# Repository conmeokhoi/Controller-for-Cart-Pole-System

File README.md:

# 150W Isolated Cart-Pole Control Board (STM32)

## 📌 Project Overview
This project presents the design and implementation of a specialized control board for an Inverted Pendulum on a Cart (Cart-Pole) system. It serves as a benchmark for testing cascaded control strategies in highly non-linear, unstable, and under-actuated environments.

## 🛠 Hardware Architecture

### 1. Multi-Stage Power Management
The system operates on a primary **24V DC** input with hierarchical regulation to ensure signal stability and efficiency:
* **12V Rail**: Regulated by the **L7812** for MOSFET gate drivers.
* **5V Auxiliary Rail**: Stepped down via a high-efficiency **TPS5430 Buck Converter** (~90% efficiency) to power encoders and sensors.
* **Isolated 3.3V Logic**: Utilizes a **B0505S** isolated DC-DC converter and an **AMS1117-3.3** LDO to shield the MCU from power-stage inductive switching noise.

### 2. Motor Drive Stage (150W H-Bridge)
* **MOSFET Selection**: Features four **IRF3205S** N-channel MOSFETs with an exceptionally low $R_{DS(on)} \approx 8 m\Omega$ to minimize conduction losses.
* **Gate Driving**: Employs **IR2104** drivers with bootstrap circuitry to maintain high-side gate saturation.
* **Safety Logic**: Integrated **520ns hardware dead-time** prevents "shoot-through" short circuits.

### 3. Galvanic Isolation
* **High-Speed Paths**: **6N137 optocouplers** (10Mbps) are dedicated to PWM and Encoder signals to prevent propagation delay in the real-time control loop.
* **Isolation Barrier**: Complete physical partitioning between the Power Zone and Clean Logic Zone via the optocoupler bridge.

## 💻 Firmware & Control Logic
Powered by the **STM32F103C8T6** (ARM Cortex-M3) at **72MHz**:
* **Encoder Processing**: Utilizes hardware Timer Encoder Mode for high-resolution quadrature decoding without CPU overhead.
* **PWM Configuration**: Frequency set at **20kHz** to eliminate audible jitter and provide granular torque control:
  $$f_{PWM} = \frac{f_{CLK}}{(PSC+1) \times (ARR+1)} = \frac{72,000,000}{36 \times 100} = 20,000 \text{ Hz}$$
* **Control Algorithm**: Implements a **Cascaded PID** structure where the outer loop manages cart position and the inner loop stabilizes the pendulum angle.

## 🔍 Failure Analysis (Root Cause)
During integration, a hardware breakdown occurred in the H-bridge. Forensic analysis identified a missing connection between the **VS pin** (Pin 6) of the IR2104 drivers and the **source terminals** of the high-side MOSFETs.This led to a "floating gate" state, causing a direct short-circuit from the 24V rail to Ground.

## 🎥 Experimental Validation
The following video demonstrates the individual functional verification of the control board:
* **Hardware Self-Test:** Verification of the 24V, 12V, 5V, and 3.3V power rails.
* **Encoder & Sensor Feedback:** Real-time pulse capturing and gyroscope data retrieval.
* **PWM Output:** Validation of 20kHz complementary signals via oscilloscope.
* **Video Demo:** 

---
**Author**: Nguyễn Huỳnh Khôi.  
**Supervised by**: PhD. Võ Lâm Chương.   
**University**: Ho Chi Minh City University of Technology and Engineering (HCMUTE)

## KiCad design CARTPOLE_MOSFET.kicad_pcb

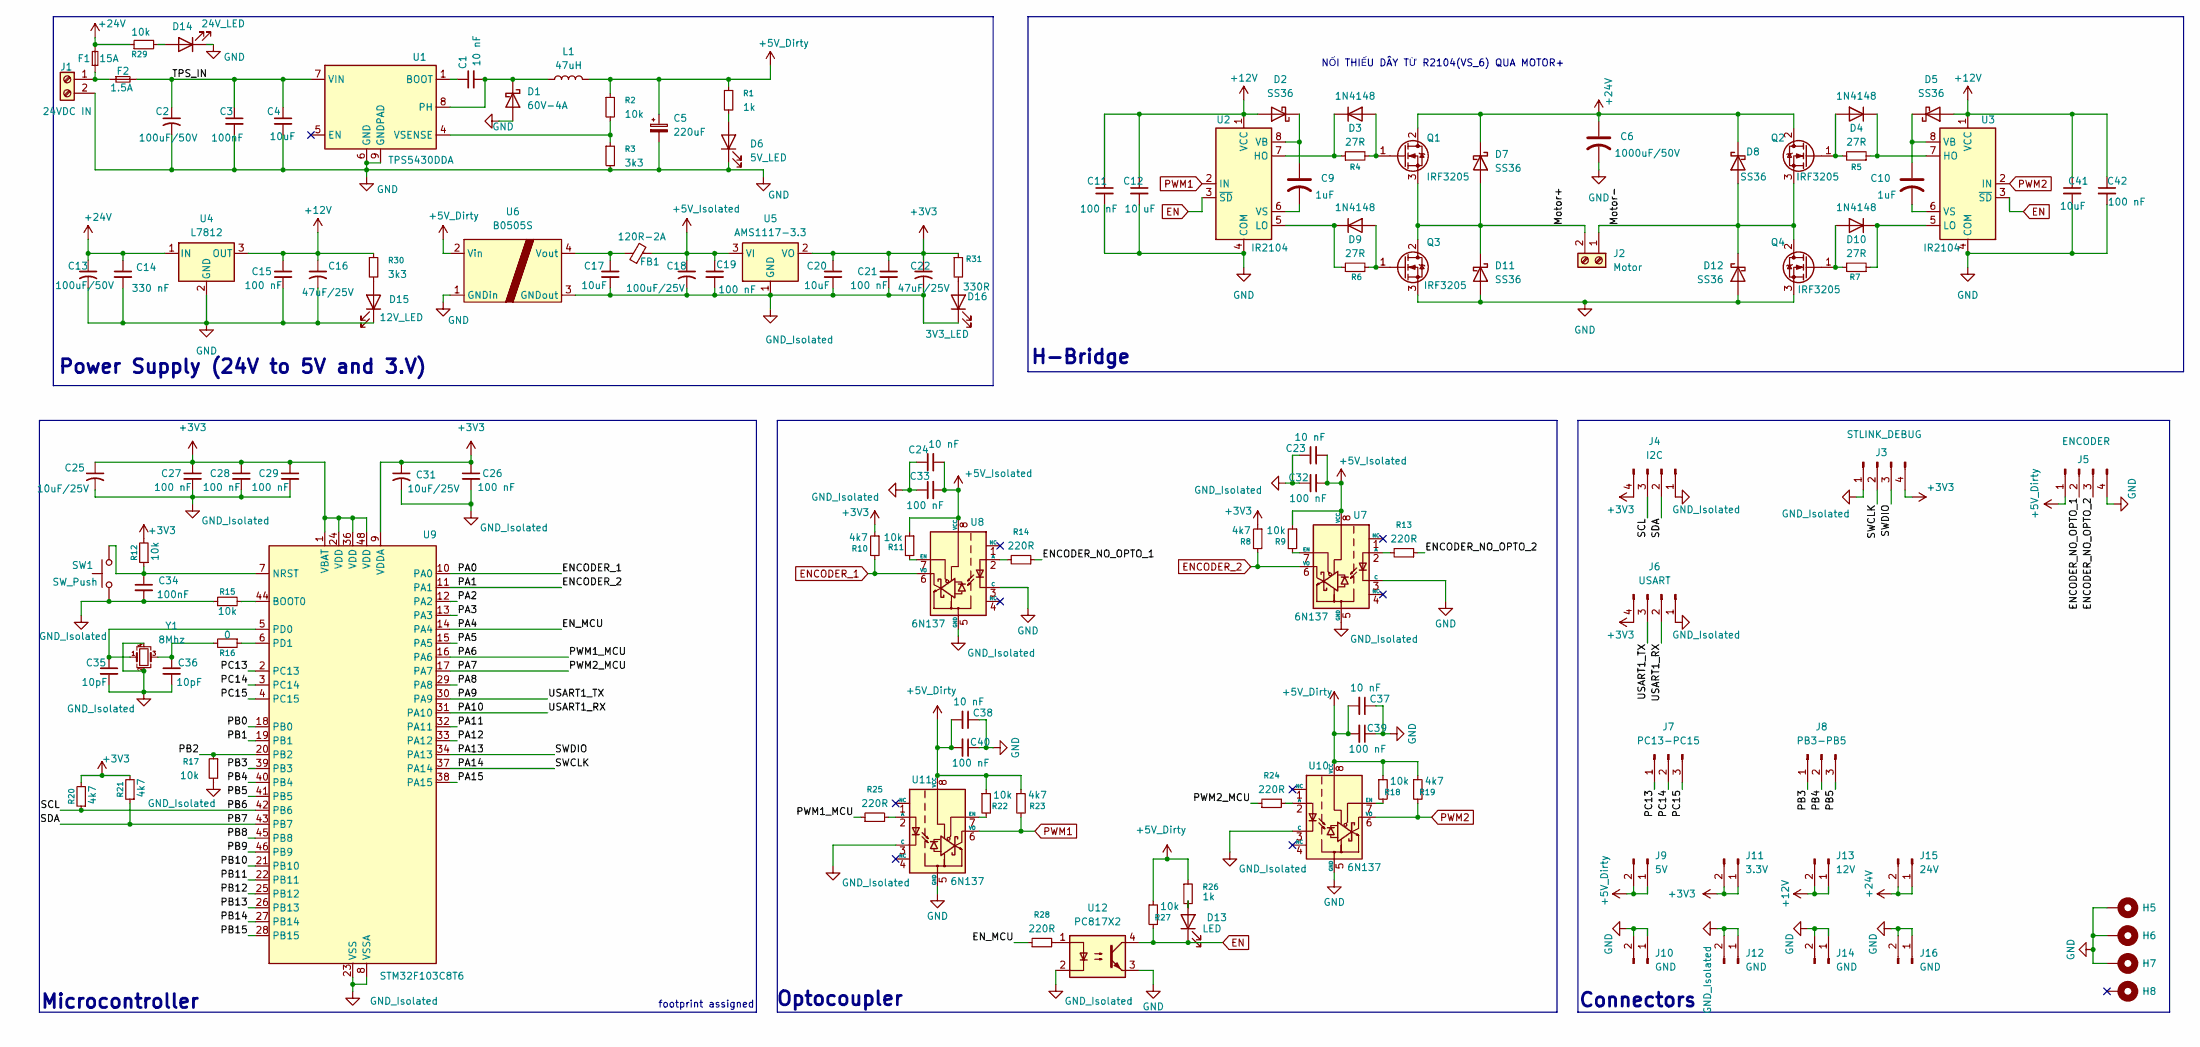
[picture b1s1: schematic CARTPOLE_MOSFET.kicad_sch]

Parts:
C1, C23, C24, C37, C38: 10 nF; C_0805_2012Metric_Pad1.18x1.45mm_HandSolder
C2, C13: 100uF/50V; CP_Elec_8x10.5
C3: 100nF; C_0805_2012Metric_Pad1.18x1.45mm_HandSolder
C4, C17, C20, C41: 10uF; C_0805_2012Metric_Pad1.18x1.45mm_HandSolder
C5: 220uF; CP_Elec_8x10.5
C6: 1000uF/50V; C_Radial_D12.5mm_H25.0mm_P5.00mm
C9, C10: 1uF; C_0805_2012Metric_Pad1.18x1.45mm_HandSolder
C11, C15, C19, C21, C32, C33, C39, C40, C42: 100 nF; C_0805_2012Metric_Pad1.18x1.45mm_HandSolder
C12: 10 uF; C_0805_2012Metric_Pad1.18x1.45mm_HandSolder
C14: 330 nF; C_0805_2012Metric_Pad1.18x1.45mm_HandSolder
C16, C22: 47uF/25V; CP_Elec_6.3x5.4
C18: 100uF/25V; CP_Elec_8x10.5
C25, C31: 10uF/25V; C_0603_1608Metric
C26, C27, C28, C29: 100 nF; C_0603_1608Metric
C34: 100nF; C_0603_1608Metric
C35, C36: 10pF; C_0603_1608Metric
D1: 60V-4A; D_SMB
D2, D5, D7, D8, D11, D12: SS36; D_SMA_Handsoldering
D3, D4, D9, D10: 1N4148; D_SOD-123
D6: 5V_LED; LED_0805_2012Metric_Pad1.15x1.40mm_HandSolder
D13: LED; LED_0805_2012Metric_Pad1.15x1.40mm_HandSolder
D14: 24V_LED; LED_0805_2012Metric_Pad1.15x1.40mm_HandSolder
D15: 12V_LED; LED_0805_2012Metric_Pad1.15x1.40mm_HandSolder
D16: 3V3_LED; LED_0805_2012Metric_Pad1.15x1.40mm_HandSolder
F1: 15A; Fuseholder_Littelfuse_Nano2_154x
F2: 1.5A; Fuseholder_Littelfuse_Nano2_154x
FB1: 120R-2A; C_0805_2012Metric_Pad1.18x1.45mm_HandSolder
H5, H6, H7, H8: MountingHole_3.2mm_M3_Pad_Via
J1: 24VDC IN; TerminalBlock_Ningbo-Kagnex_HB9500_1x02_P9.5mm
J2: Motor; TerminalBlock_Ningbo-Kagnex_HB9500_1x02_P9.5mm
J3: STLINK_DEBUG; PinHeader_1x04_P2.54mm_Vertical
J4: I2C; PinHeader_1x04_P2.54mm_Vertical
J5: ENCODER; PinHeader_1x04_P2.54mm_Vertical
J6: USART; PinHeader_1x04_P2.54mm_Vertical
J7: PC13-PC15; PinHeader_1x03_P2.54mm_Vertical
J8: PB3-PB5; PinHeader_1x03_P2.54mm_Vertical
J9: 5V; PinHeader_1x02_P2.54mm_Vertical
J10, J12, J14, J16: GND; PinHeader_1x02_P2.54mm_Vertical
J11: 3.3V; PinHeader_1x02_P2.54mm_Vertical
J13: 12V; PinHeader_1x02_P2.54mm_Vertical
J15: 24V; PinHeader_1x02_P2.54mm_Vertical
L1: 47uH; INDPM120120X800N
Q1, Q2, Q3, Q4: IRF3205; TO-263-2
R1, R26: 1k; R_0805_2012Metric_Pad1.20x1.40mm_HandSolder
R2, R9, R11, R18, R22, R27, R29: 10k; R_0805_2012Metric_Pad1.20x1.40mm_HandSolder
R3, R30: 3k3; R_0805_2012Metric_Pad1.20x1.40mm_HandSolder
R4, R5, R6, R7: 27R; R_0805_2012Metric_Pad1.20x1.40mm_HandSolder
R8, R10, R19, R23: 4k7; R_0805_2012Metric_Pad1.20x1.40mm_HandSolder
R12, R15, R17: 10k; C_0603_1608Metric
R13, R14, R24, R25, R28: 220R; R_0805_2012Metric_Pad1.20x1.40mm_HandSolder
R16: 0; C_0603_1608Metric
R20, R21: 4k7; R_0603_1608Metric
R31: 330R; R_0805_2012Metric_Pad1.20x1.40mm_HandSolder
SW1: SW_Push; SW_SPST_CK_RS282G05A3
U1: TPS5430DDA; TI_SO-PowerPAD-8_ThermalVias
U2, U3: IR2104; SOIC-8_3.9x4.9mm_P1.27mm
U4: L7812; TO-220-3_Vertical
U5: AMS1117-3.3; SOT-223-3_TabPin2
U6: B0505S; CONV_RFM-0505S
U7, U8, U10, U11: 6N137; SMDIP-8_W9.53mm_Clearance8mm
U9: STM32F103C8T6; LQFP-48_7x7mm_P0.5mm
U12: PC817X2; SOP254P975X460-4N
Y1: 8Mhz; Crystal_SMD_3225-4Pin_3.2x2.5mm

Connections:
+3V3: C20.1, C21.1, C22.1, C25.1, C26.1, C27.1, C28.1, C29.1, C31.1, J3.4, J4.4, J6.4, J11.1, J11.2, R8.1, R10.1, R12.2, R20.2, R21.2, R31.1, U5.2 (VO), U9.1 (VBAT), U9.9 (VDDA), U9.24 (VDD), U9.36 (VDD), U9.48 (VDD)
+5V_Dirty: C5.1, C37.2, C38.2, C39.2, C40.2, J5.1, J9.1, J9.2, L1.2, R1.1, R2.1, R18.1, R19.1, R22.1, R23.1, R26.1, R27.1, U6.2 (Vin), U10.8 (VCC), U11.8 (VCC)
+5V_Isolated: C18.1, C19.1, C23.2, C24.2, C32.2, C33.2, FB1.2, R9.1, R11.1, U5.3 (VI), U7.8 (VCC), U8.8 (VCC)
+12V: C11.1, C12.1, C15.1, C16.1, C41.1, C42.1, D2.2 (A), D5.2 (A), J13.1, J13.2, R30.1, U2.1 (VCC), U3.1 (VCC), U4.3 (OUT)
+24V: C6.1, C13.1, C14.1, D7.1 (K), D8.1 (K), F1.2, J15.1, J15.2, Q1.2 (D), Q2.2 (D), R29.1, U4.1 (IN)
/ENCODER_NO_OPTO_1: J5.2, R14.1
/ENCODER_NO_OPTO_2: J5.3, R13.1
/EN_MCU: R28.1, U9.14 (PA4)
/Motor+: D7.2 (A), D11.1 (K), J2.2, Q1.3 (S), Q3.2 (D)
/Motor-: D8.2 (A), D12.1 (K), J2.1, Q2.3 (S), Q4.2 (D)
/PA2: U9.12 (PA2)
/PA3: U9.13 (PA3)
/PA5: U9.15 (PA5)
/PA6: R25.1, U9.16 (PA6)
/PA7: R24.1, U9.17 (PA7)
/PA8: U9.29 (PA8)
/PA9: J6.3, U9.30 (PA9)
/PA10: J6.2, U9.31 (PA10)
/PA11: U9.32 (PA11)
/PA12: U9.33 (PA12)
/PA13: J3.3, U9.34 (PA13)
/PA14: J3.2, U9.37 (PA14)
/PA15: U9.38 (PA15)
/PB0: U9.18 (PB0)
/PB1: U9.19 (PB1)
/PB2: R17.1, U9.20 (PB2)
/PB3: J8.1, U9.39 (PB3)
/PB4: J8.2, U9.40 (PB4)
/PB5: J8.3, U9.41 (PB5)
/PB6: J4.3, R20.1, U9.42 (PB6)
/PB7: J4.2, R21.1, U9.43 (PB7)
/PB8: U9.45 (PB8)
/PB9: U9.46 (PB9)
/PB10: U9.21 (PB10)
/PB11: U9.22 (PB11)
/PB12: U9.25 (PB12)
/PB13: U9.26 (PB13)
/PB14: U9.27 (PB14)
/PB15: U9.28 (PB15)
/PC13: J7.1, U9.2 (PC13)
/PC14: J7.2, U9.3 (PC14)
/PC15: J7.3, U9.4 (PC15)
/TPS_IN: C2.1, C3.1, C4.1, F2.2, U1.7 (VIN)
EN: D13.1 (K), R27.2, U2.3 (~SD), U3.3 (~SD), U12.4
ENCODER_1: R10.2, U8.6 (VO), U9.10 (PA0)
ENCODER_2: R8.2, U7.6 (VO), U9.11 (PA1)
GND: C2.2, C3.2, C4.2, C5.2, C6.2, C11.2, C12.2, C13.2, C14.2, C15.2, C16.2, C37.1, C38.1, C39.1, C40.1, C41.2, C42.2, D1.2 (A), D6.1 (K), D11.2 (A), D12.2 (A), D14.1 (K), D15.1 (K), H5.1, H6.1, H7.1, J1.2, J5.4, J10.1, J10.2, J14.1, J14.2, J16.1, J16.2, Q3.3 (S), Q4.3 (S), R3.2, U1.6 (GND), U1.9 (GNDPAD), U2.4 (COM), U3.4 (COM), U4.2 (GND), U6.1 (GNDin), U7.3 (C), U8.3 (C), U10.5 (GND), U11.5 (GND), U12.3
GND_Isolated: C17.2, C18.2, C19.2, C20.2, C21.2, C22.2, C23.1, C24.1, C25.2, C26.2, C27.2, C28.2, C29.2, C31.2, C32.1, C33.1, C34.2, C35.2, C36.2, D16.1 (K), J3.1, J4.1, J6.1, J12.1, J12.2, R15.1, R17.2, SW1.1, U5.1 (GND), U6.3 (GNDout), U7.5 (GND), U8.5 (GND), U9.8 (VSSA), U9.23 (VSS), U9.35 (VSS), U9.47 (VSS), U10.3 (C), U11.3 (C), U12.2, Y1.2, Y1.4
unnamed: C36.1, R16.2, Y1.3
unnamed: C1.2, D1.1 (K), L1.1, U1.8 (PH)
unnamed: C9.1, D2.1 (K), U2.8 (VB)
unnamed: D3.2 (A), Q1.1 (G), R4.2
unnamed: D3.1 (K), R4.1, U2.7 (HO)
unnamed: D4.2 (A), Q2.1 (G), R5.2
unnamed: D4.1 (K), R5.1, U3.7 (HO)
unnamed: C10.1, D5.1 (K), U3.8 (VB)
unnamed: D6.2 (A), R1.2
unnamed: D9.2 (A), Q3.1 (G), R6.2
unnamed: D9.1 (K), R6.1, U2.5 (LO)
unnamed: D10.2 (A), Q4.1 (G), R7.2
unnamed: D10.1 (K), R7.1, U3.5 (LO)
unnamed: D13.2 (A), R26.2
unnamed: D14.2 (A), R29.2
unnamed: D15.2 (A), R30.2
unnamed: D16.2 (A), R31.2
unnamed: F1.1, F2.1, J1.1
unnamed: R28.2, U12.1
unnamed: C1.1, U1.1 (BOOT)
unnamed: R2.2, R3.1, U1.4 (VSENSE)
unnamed: C9.2, U2.6 (VS)
unnamed: C10.2, U3.6 (VS)
unnamed: C17.1, FB1.1, U6.4 (Vout)
unnamed: R13.2, U7.2 (A)
unnamed: R9.2, U7.7 (EN)
unnamed: R14.2, U8.2 (A)
unnamed: R11.2, U8.7 (EN)
unnamed: R15.2, U9.44 (BOOT0)
unnamed: C34.1, R12.1, SW1.2, U9.7 (NRST)
unnamed: C35.1, U9.5 (PD0), Y1.1
unnamed: R16.1, U9.6 (PD1)
unnamed: R24.2, U10.2 (A)
unnamed: R18.2, U10.7 (EN)
unnamed: R25.2, U11.2 (A)
unnamed: R22.2, U11.7 (EN)
PWM1: R23.2, U2.2 (IN), U11.6 (VO)
PWM2: R19.2, U3.2 (IN), U10.6 (VO)

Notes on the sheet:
Connectors
Microcontroller
footprint assigned
H-Bridge
Power Supply (24V to 5V and 3.V)
Optocoupler
NỐI THIẾU DÂY TỪ R2104(VS_6) QUA MOTOR+

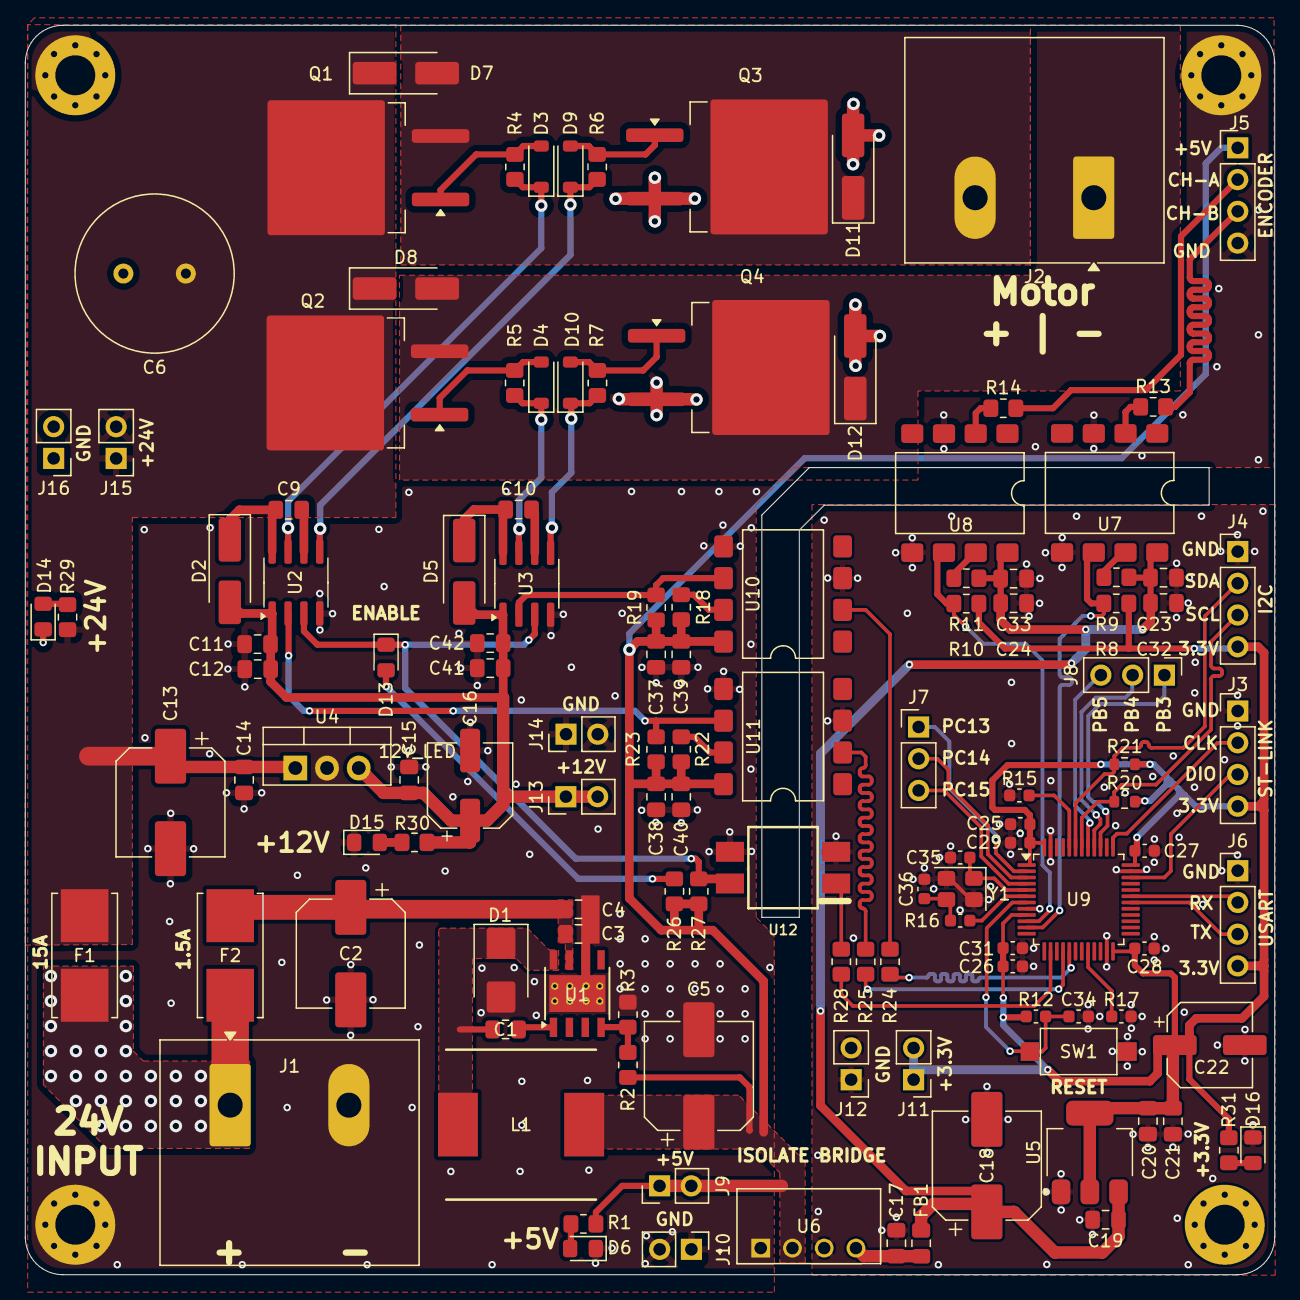
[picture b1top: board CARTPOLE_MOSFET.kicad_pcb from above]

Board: 2 copper layers, 100.0 x 100.0 mm, 128 parts (0 on the bottom side), 69 nets.

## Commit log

2026-03-18 Update README with detailed project description
    Expanded project description with detailed specifications and features.
2026-03-18 Enhance README with project overview and architecture
    Expanded project documentation to include detailed hardware architecture, firmware logic, and failure analysis.
2026-03-18 Refactor README for clarity and formatting
    Removed citation markers from project overview and hardware architecture sections for clarity. Improved formatting for better readability.
2026-03-18 Fix formatting of author and supervision details
2026-03-18 Revise video demo section in README
    Updated video demo link and removed old report link.
2026-03-19 Update README with schematic and board images
    Added images of the schematic and board views to the README, enhancing documentation with visual references.
